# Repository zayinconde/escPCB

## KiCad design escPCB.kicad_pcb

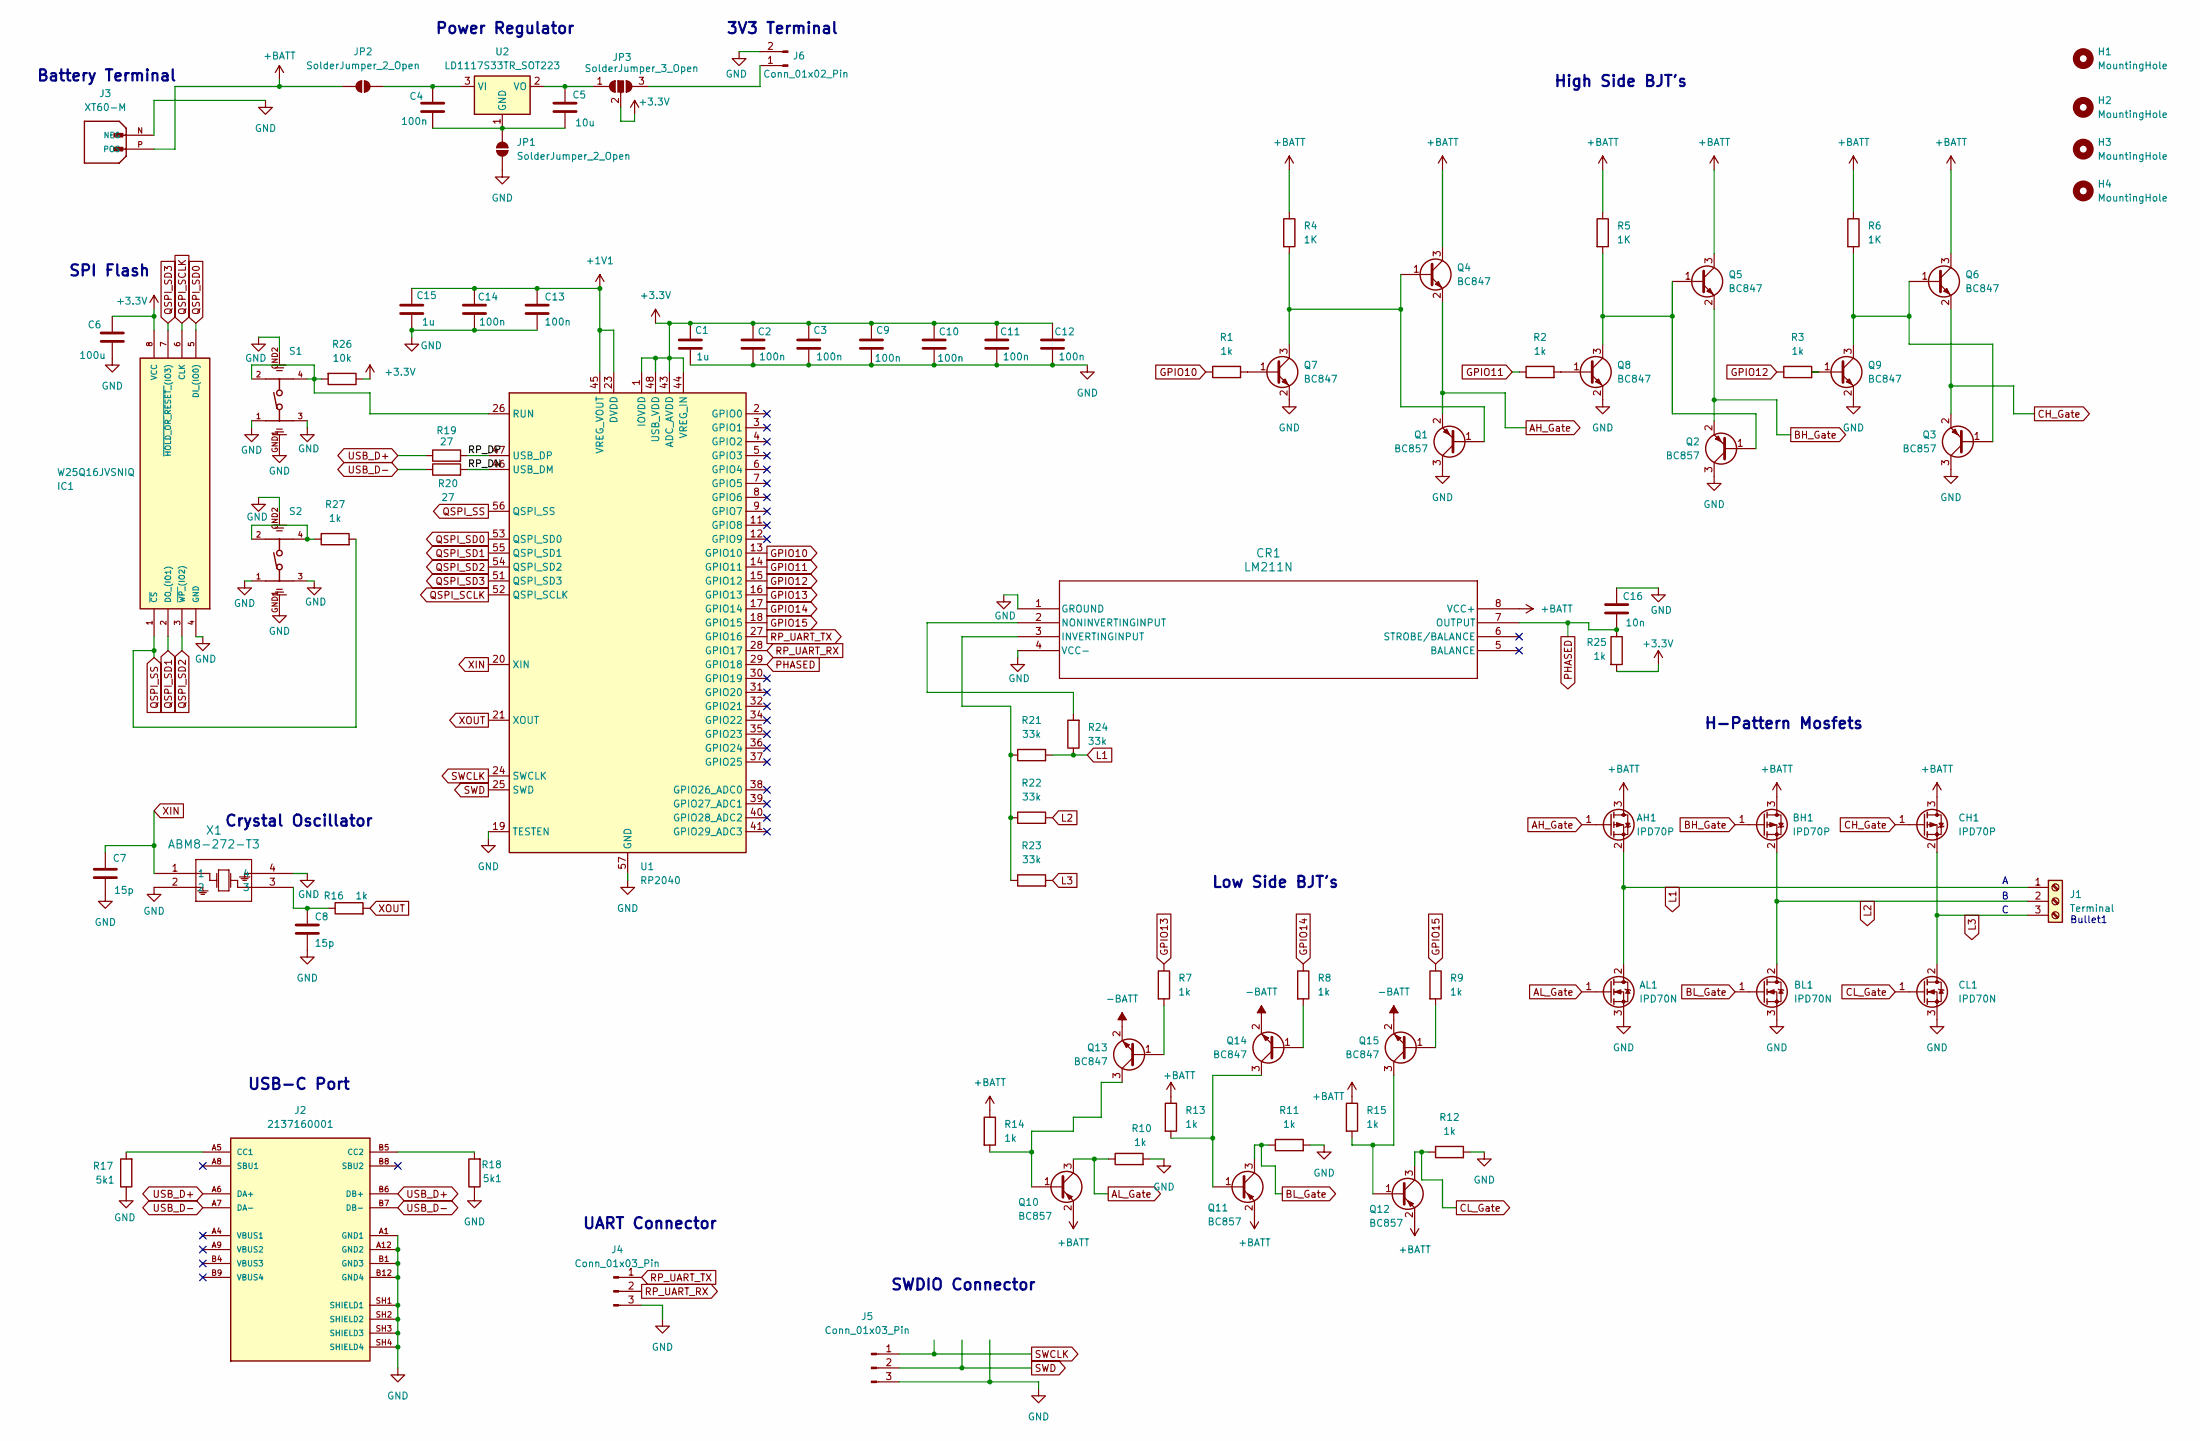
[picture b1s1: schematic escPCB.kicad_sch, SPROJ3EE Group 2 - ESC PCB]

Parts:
AH1: IPD70P; IPD70P04P4L08ATMA2
AL1: IPD70N; IPB70N12S311ATMA1
BH1: IPD70P; IPD70P04P4L08ATMA2
BL1: IPD70N; IPB70N12S311ATMA1
C1, C15: 1u; C_0805_2012Metric
C2, C3, C4, C9, C10, C11, C12, C13, C14: 100n; C_0805_2012Metric
C5: 10u; C_0805_2012Metric
C6: 100u; C_0805_2012Metric
C7, C8: 15p; C_0805_2012Metric
C16: 10n; C_0805_2012Metric
CH1: IPD70P; IPD70P04P4L08ATMA2
CL1: IPD70N; IPB70N12S311ATMA1
CR1: LM211N; DIP-8_STM
H1, H2, H3, H4: MountingHole; MountingHole_3.2mm_M3
IC1: W25Q16JVSNIQ; W25Q; MOUSER_PART_NUMBER 454-W25Q16JVSNIQ
J1: Terminal; TerminalBlock_Altech_AK300-3_P5.00mm
J2: 2137160001; MOLEX_2137160001 USB-C; PARTREV B
J3: XT60-M; AMASS_XT60-M; PARTREV V1.2
J4, J5: Conn_01x03_Pin; JST_PH_S3B-PH-K_1x03_P2.00mm_Horizontal
J6: Conn_01x02_Pin; JST_PH_S2B-PH-K_1x02_P2.00mm_Horizontal
JP1, JP2: SolderJumper_2_Open; SolderJumper-2_P1.3mm_Open_RoundedPad1.0x1.5mm
JP3: SolderJumper_3_Open; SolderJumper-3_P1.3mm_Open_Pad1.0x1.5mm_NumberLabels
Q1, Q2, Q3, Q10, Q11, Q12: BC857; SOT-23
Q4, Q5, Q6, Q7, Q8, Q9, Q13, Q14, Q15: BC847; SOT-23
R1, R2, R3, R7, R8, R9, R10, R11, R12, R13, R14, R15, R16, R25, R27: 1k; R_0805_2012Metric
R4, R5, R6: 1K; R_0805_2012Metric
R17, R18: 5k1; R_0805_2012Metric
R19, R20: 27; R_0805_2012Metric
R21, R22, R23, R24: 33k; R_0805_2012Metric
R26: 10k; R_0805_2012Metric
S1, S2: 431183015816; PART-NUMBER 431183015816
U1: RP2040; QFN-56-1EP_7x7mm_P0.4mm_EP3.2x3.2mm
U2: LD1117S33TR_SOT223; SOT-223-3_TabPin2
X1: ABM8-272-T3; ABM8-272-T3_ABR

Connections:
+1V1: C13.1, C14.1, C15.1, U1.23 (DVDD), U1.45 (VREG_VOUT), U1.50 (DVDD)
+3.3V: C1.1, C2.1, C3.1, C6.1, C9.1, C10.1, C11.1, C12.1, IC1.8 (VCC), JP3.2 (C), R25.2, R26.1, U1.1 (IOVDD), U1.10 (IOVDD), U1.22 (IOVDD), U1.33 (IOVDD), U1.42 (IOVDD), U1.43 (ADC_AVDD), U1.44 (VREG_IN), U1.48 (USB_VDD), U1.49 (IOVDD)
+BATT: AH1.3 (D), BH1.3 (D), CH1.3 (D), CR1.8 (VCC+), J3.P (POS), JP2.2 (B), Q4.3 (C), Q5.3 (C), Q6.3 (C), Q10.2 (E), Q11.2 (E), Q12.2 (E), R4.1, R5.1, R6.1, R13.1, R14.1, R15.1
-BATT: Q13.2 (E), Q14.2 (E), Q15.2 (E)
/RP_DN: R20.2, U1.46 (USB_DM)
/RP_DP: R19.2, U1.47 (USB_DP)
AH_Gate: AH1.1 (G), Q1.2 (E), Q4.2 (E)
AL_Gate: AL1.1 (G), Q10.3 (C), R10.1
BH_Gate: BH1.1 (G), Q2.2 (E), Q5.2 (E)
BL_Gate: BL1.1 (G), Q11.3 (C), R11.1
CH_Gate: CH1.1 (G), Q3.2 (E), Q6.2 (E)
CL_Gate: CL1.1 (G), Q12.3 (C), R12.1
GND: AL1.3 (S), BL1.3 (S), C1.2, C2.2, C3.2, C6.2, C7.2, C8.2, C9.2, C10.2, C11.2, C12.2, C13.2, C14.2, C15.2, C16.2, CL1.3 (S), CR1.1 (GROUND), CR1.4 (VCC-), IC1.4 (GND), J2.A1 (GND1), J2.A12 (GND2), J2.B1 (GND3), J2.B12 (GND4), J2.SH1 (SHIELD1), J2.SH2 (SHIELD2), J2.SH3 (SHIELD3), J2.SH4 (SHIELD4), J3.N (NEG), J4.3, J5.3, J6.2, JP1.1 (A), Q1.3 (C), Q2.3 (C), Q3.3 (C), Q7.2 (E), Q8.2 (E), Q9.2 (E), R10.2, R11.2, R12.2, R17.1, R18.1, S1.1, S1.3, S1.GND1, S1.GND2, S2.1, S2.3, S2.GND1, S2.GND2, U1.19 (TESTEN), U1.57 (GND), X1.2, X1.4
GPIO10: R1.1, U1.13 (GPIO10)
GPIO11: R2.1, U1.14 (GPIO11)
GPIO12: R3.1, U1.15 (GPIO12)
GPIO13: R7.1, U1.16 (GPIO13)
GPIO14: R8.1, U1.17 (GPIO14)
GPIO15: R9.1, U1.18 (GPIO15)
L1: AH1.2 (S), AL1.2 (D), J1.1, R21.2, R24.1
L2: BH1.2 (S), BL1.2 (D), J1.2, R22.2
L3: CH1.2 (S), CL1.2 (D), J1.3, R23.2
unnamed: C8.1, R16.1, X1.3
unnamed: CR1.3 (INVERTINGINPUT), R21.1, R22.1, R23.1
unnamed: CR1.2 (NONINVERTINGINPUT), R24.2
unnamed: J2.A5 (CC1), R17.2
unnamed: J2.B5 (CC2), R18.2
unnamed: J6.1, JP3.3 (B)
unnamed: C4.2, C5.2, JP1.2 (B), U2.1 (GND)
unnamed: C4.1, JP2.1 (A), U2.3 (VI)
unnamed: C5.1, JP3.1 (A), U2.2 (VO)
unnamed: Q1.1 (B), Q4.1 (B), Q7.3 (C), R4.2
unnamed: Q2.1 (B), Q5.1 (B), Q8.3 (C), R5.2
unnamed: Q3.1 (B), Q6.1 (B), Q9.3 (C), R6.2
unnamed: Q7.1 (B), R1.2
unnamed: Q8.1 (B), R2.2
unnamed: Q9.1 (B), R3.2
unnamed: Q10.1 (B), Q13.3 (C), R14.2
unnamed: Q11.1 (B), Q14.3 (C), R13.2
unnamed: Q12.1 (B), Q15.3 (C), R15.2
unnamed: Q13.1 (B), R7.2
unnamed: Q14.1 (B), R8.2
unnamed: Q15.1 (B), R9.2
unnamed: R27.1, S2.2, S2.4
unnamed: R26.2, S1.2, S1.4, U1.26 (RUN)
PHASED: C16.1, CR1.7 (OUTPUT), R25.1, U1.29 (GPIO18)
QSPI_SCLK: IC1.6 (CLK), U1.52 (QSPI_SCLK)
QSPI_SD0: IC1.5 (DI_(IO0)), U1.53 (QSPI_SD0)
QSPI_SD1: IC1.2 (DO_(IO1)), U1.55 (QSPI_SD1)
QSPI_SD2: IC1.3 (~WP_(IO2)), U1.54 (QSPI_SD2)
QSPI_SD3: IC1.7 (~HOLD_OR_~RESET_(IO3)), U1.51 (QSPI_SD3)
QSPI_SS: IC1.1 (~CS), R27.2, U1.56 (QSPI_SS)
RP_UART_RX: J4.2, U1.28 (GPIO17)
RP_UART_TX: J4.1, U1.27 (GPIO16)
SWCLK: J5.1, U1.24 (SWCLK)
SWD: J5.2, U1.25 (SWD)
USB_D+: J2.A6 (DA+), J2.B6 (DB+), R19.1
USB_D-: J2.A7 (DA-), J2.B7 (DB-), R20.1
XIN: C7.1, U1.20 (XIN), X1.1
XOUT: R16.2, U1.21 (XOUT)

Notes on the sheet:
High Side BJT's
SWDIO Connector
Low Side BJT's
Power Regulator
UART Connector
USB-C Port
H-Pattern Mosfets
Crystal Oscillator
Bullet1
SPI Flash
Battery Terminal
3V3 Terminal

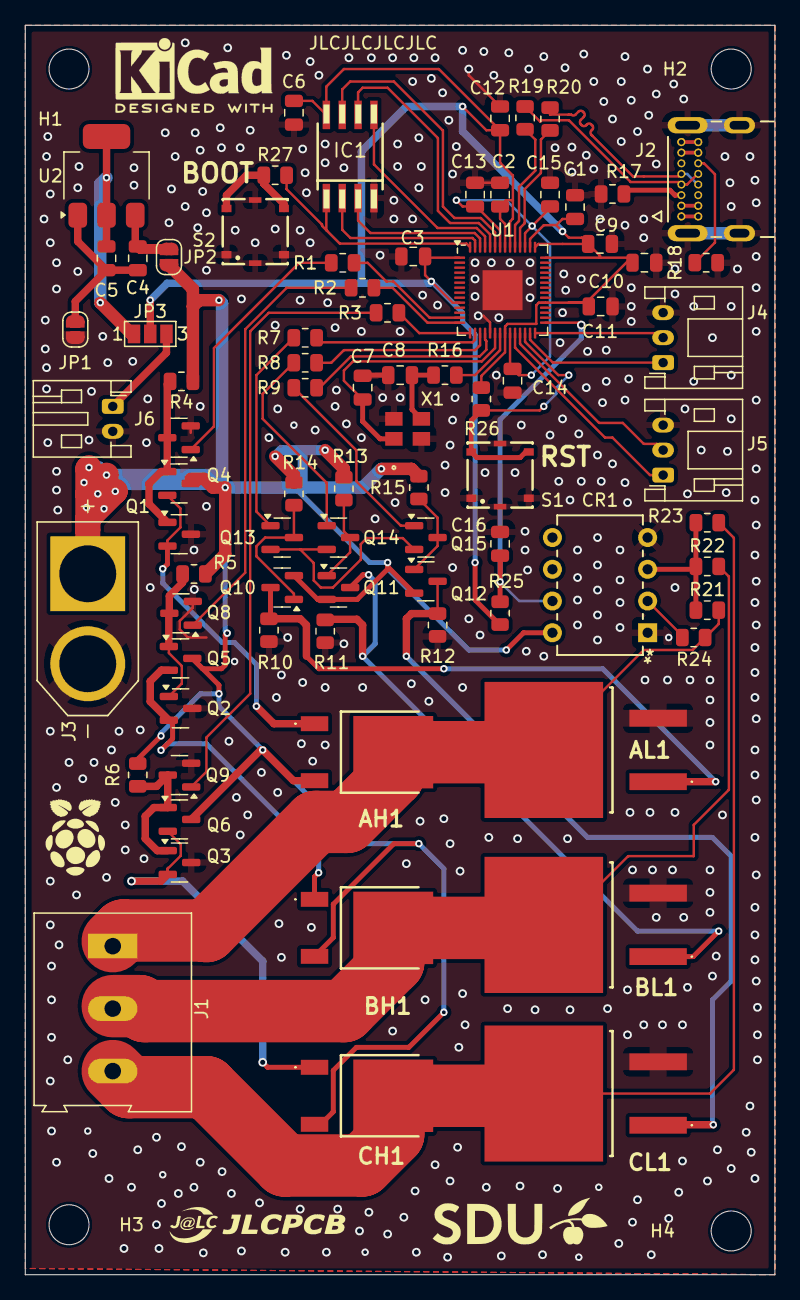
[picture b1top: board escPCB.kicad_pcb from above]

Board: 2 copper layers, 60.0 x 100.0 mm, 84 parts (0 on the bottom side), 60 nets.

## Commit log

2024-11-19 schematics v1
2024-11-25 schematic v2 with some footprints
2024-11-25 v3 PCB design from Desktop
    Had to upload differently cause it was made on my desktop
2024-11-25 additional footprints needed
2024-11-25 updating from repo
2024-11-27 final version
2024-12-04 with 3d print casing
2024-12-12 Simulations
